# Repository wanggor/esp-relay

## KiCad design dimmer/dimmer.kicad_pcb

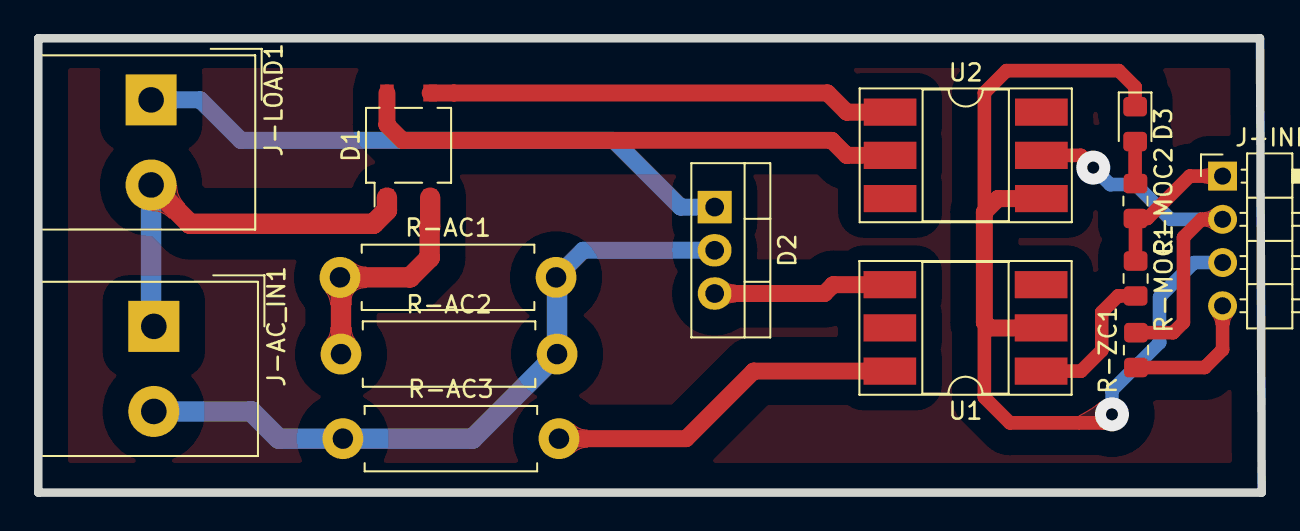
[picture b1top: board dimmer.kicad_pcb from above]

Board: 2 copper layers, 71.9 x 26.7 mm, 14 parts (0 on the bottom side), 14 nets.

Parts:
D1: MB6S; TO-269AA
D2: Q_TRIAC_A1A2G; TO-220-3_Vertical
D3: LED; LED_0805_2012Metric_Pad1.15x1.40mm_HandSolder
J-AC_IN1: Conn_01x02_Male; Altech_AK300_1x02_P5.00mm_45-Degree
J-INPUT1: Conn_01x04_Male; PinHeader_1x04_P2.54mm_Horizontal
J-LOAD1: Conn_01x02_Male; Altech_AK300_1x02_P5.00mm_45-Degree
R-AC1, R-AC2: 59K; R_Axial_DIN0411_L9.9mm_D3.6mm_P12.70mm_Horizontal
R-AC3: 1K; R_Axial_DIN0411_L9.9mm_D3.6mm_P12.70mm_Horizontal
R-MOC1: 471; R_0805_2012Metric_Pad1.15x1.40mm_HandSolder
R-MOC2: 331; R_0805_2012Metric_Pad1.15x1.40mm_HandSolder
R-ZC1: 10K; R_0805_2012Metric_Pad1.15x1.40mm_HandSolder
U1: MOC3021M; DIP-6_W8.89mm_SMDSocket_LongPads
U2: 4N35; DIP-6_W8.89mm_SMDSocket_LongPads

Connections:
/AC_CON: R-AC3.2, U1.6
/AC_IN-L: D2.2, J-AC_IN1.2, R-AC1.2, R-AC2.2, R-AC3.1
/AC_IN-N: D1.1, J-AC_IN1.1, J-LOAD1.2
/AC_IN-P: D1.2, R-AC1.1, R-AC2.1
/AC_LOAD: D2.1, J-LOAD1.1
/CON_GATE: D2.3, U1.4
/PWM: J-INPUT1.1, R-MOC1.1, R-MOC2.2
/Z-C: J-INPUT1.2, R-ZC1.2, U2.5
GND: D3.1, J-INPUT1.3, U1.2, U2.4
GNDPWR: D1.4, U2.2
unnamed: D3.2, R-MOC2.1
unnamed: R-MOC1.2, U1.1
VCC: J-INPUT1.4, R-ZC1.1
VPP: D1.3, U2.1

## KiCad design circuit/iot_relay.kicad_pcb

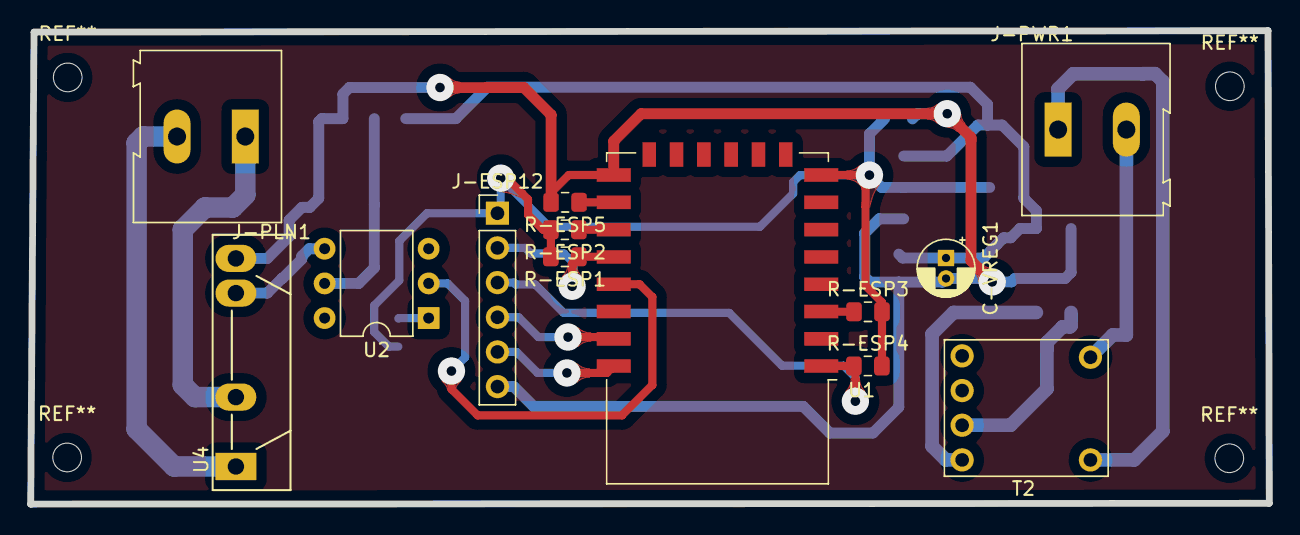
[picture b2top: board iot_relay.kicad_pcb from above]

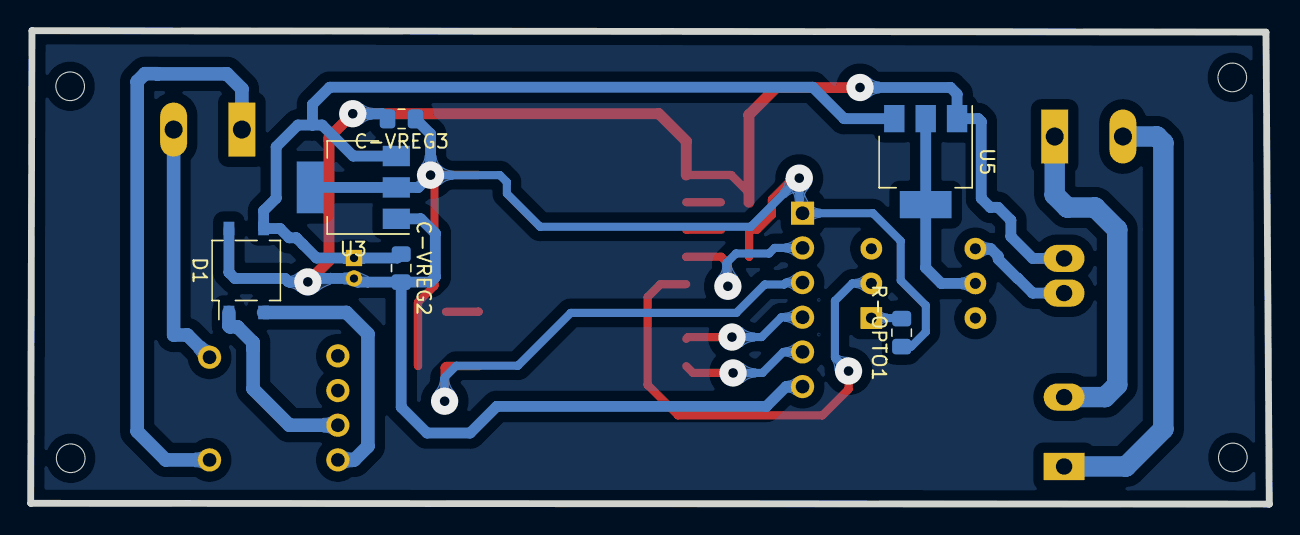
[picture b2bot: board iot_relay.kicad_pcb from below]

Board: 2 copper layers, 90.7 x 34.7 mm, 19 parts (6 on the bottom side), 20 nets.

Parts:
C-VREG1: CP; CP_Radial_D4.0mm_P1.50mm
C-VREG2, C-VREG3: C; C_0805_2012Metric_Pad1.15x1.40mm_HandSolder
D1: MB6S; TO-269AA
J-ESP12: Conn_01x06_Male; PinHeader_1x06_P2.54mm_Vertical
J-PLN1: Conn_01x02_Male; TerminalBlock_Altech_AK300-2_P5.00mm
J-PWR1: Conn_01x02_Male; TerminalBlock_Altech_AK300-2_P5.00mm
R-ESP1, R-ESP2, R-ESP3, R-ESP4, R-ESP5: 10K; R_0805_2012Metric_Pad1.15x1.40mm_HandSolder
R-OPTO1: 330; R_0805_2012Metric_Pad1.15x1.40mm_HandSolder
T2: Transformer_1P_2S; charger_transformator_a
U1: ESP-12F; ESP-12E
U2: 4N35; DIP-6_W7.62mm
U3: AMS1117-3.3; SOT-223-3_TabPin2
U4: S216S01; SIP4_Sharp-SSR_P7.62mm_Straight
U5: AMS1117-5.0; SOT-223-3_TabPin2

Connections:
/EN: R-ESP3.1, U1.3
/P0: J-ESP12.2, R-ESP1.1, U1.18
/P2: R-ESP2.1, U1.17
/P15: R-ESP5.1, U1.16
/P_RELAY: U1.19, U2.2
/RST: J-ESP12.3, R-ESP4.1, U1.1
/RXD: J-ESP12.4, U1.21
/TXD: J-ESP12.5, U1.22
GND: C-VREG1.2, C-VREG2.2, C-VREG3.2, D1.4, J-ESP12.6, R-ESP5.2, U1.15, U3.1, U4.4, U5.1
unnamed: C-VREG1.1, C-VREG2.1, D1.3, U3.3, U5.3
unnamed: D1.1, T2.4
unnamed: D1.2, T2.3
unnamed: J-PLN1.1, U4.2
unnamed: J-PLN1.2, U4.1
unnamed: J-PWR1.1, T2.1
unnamed: J-PWR1.2, T2.2
unnamed: R-OPTO1.2, U2.1
unnamed: U2.4, U4.3
VCC: U2.5, U5.2
VDD: C-VREG3.1, J-ESP12.1, R-ESP1.2, R-ESP2.2, R-ESP3.2, R-ESP4.2, R-OPTO1.1, U1.8, U3.2

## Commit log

2020-06-14 preliminary circuit
2020-07-05 dimmer
2021-01-19 afis
